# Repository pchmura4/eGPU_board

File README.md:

# eGPU_board
eGPU PCI-e adapter to give the second chance to an old laptop.  
Tested with external power (step-up converter unpopulated)

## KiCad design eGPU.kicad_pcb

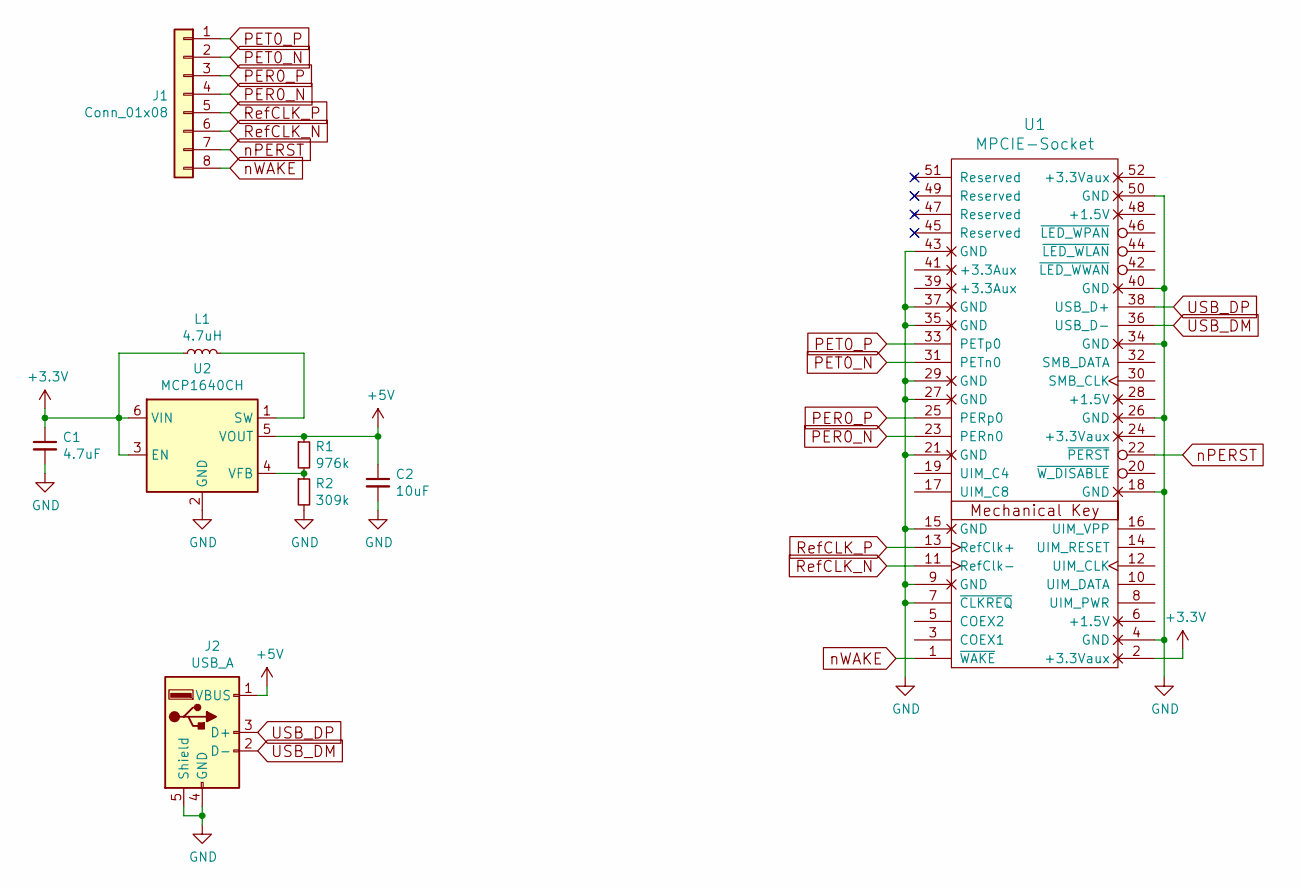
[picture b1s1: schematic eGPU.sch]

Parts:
C1: 4.7uF; C_0603
C2: 10uF; C_0805
J1: Conn_01x08; Pin_Header_Angled_1x08_Pitch1.00mm
J2: USB_A
L1: 4.7uH; L_1210
R1: 976k; R_0603
R2: 309k; R_0603
U1: MPCIE-Socket; mpcie-half-card
U2: MCP1640CH; SOT-23-6

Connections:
+3V3: C1.1, L1.1, U1.2 (+3.3Vaux), U2.3 (EN), U2.6 (VIN)
+5V: C2.1, J2.1 (VBUS), R1.1, U2.5 (VOUT)
GND: C1.2, C2.2, J2.4 (GND), J2.5 (Shield), R2.2, U1.4 (GND), U1.7 (~CLKREQ), U1.9 (GND), U1.15 (GND), U1.18 (GND), U1.21 (GND), U1.26 (GND), U1.27 (GND), U1.29 (GND), U1.34 (GND), U1.35 (GND), U1.37 (GND), U1.40 (GND), U1.43 (GND), U1.50 (GND), U2.2 (GND)
unnamed: L1.2, U2.1 (SW)
unnamed: R1.2, R2.1, U2.4 (VFB)
PER0_N: J1.4, U1.23 (PERn0)
PER0_P: J1.3, U1.25 (PERp0)
PET0_N: J1.2, U1.31 (PETn0)
PET0_P: J1.1, U1.33 (PETp0)
RefCLK_N: J1.6, U1.11 (RefClk-)
RefCLK_P: J1.5, U1.13 (RefClk+)
USB_DM: J2.2 (D-), U1.36 (USB_D-)
USB_DP: J2.3 (D+), U1.38 (USB_D+)
nPERST: J1.7, U1.22 (~PERST)
nWAKE: J1.8, U1.1 (~WAKE)

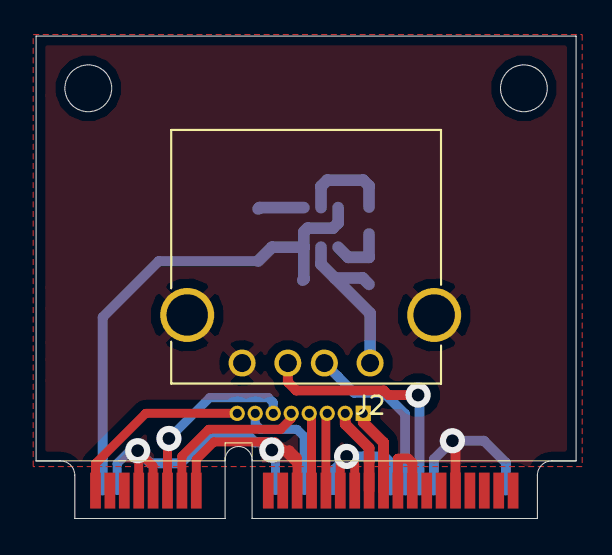
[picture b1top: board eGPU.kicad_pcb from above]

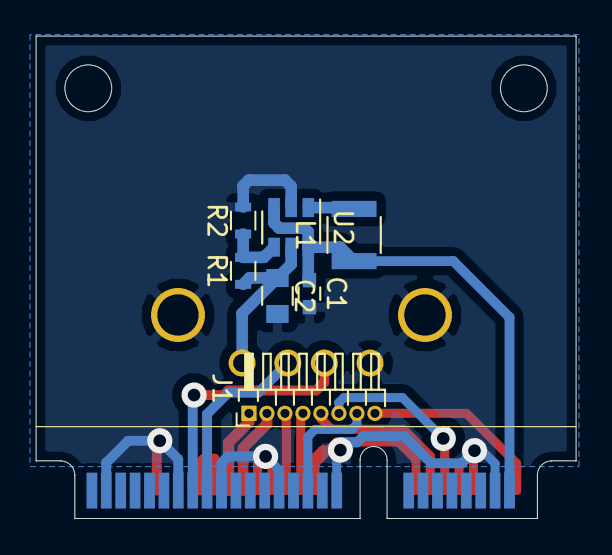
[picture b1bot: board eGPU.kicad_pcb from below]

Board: 2 copper layers, 30.0 x 26.8 mm, 9 parts (7 on the bottom side), 15 nets.

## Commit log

2021-02-15 Fixed typo
